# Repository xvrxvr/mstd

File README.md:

# UKNC-BK MSTD+

**UKNC-BK MSTD+** is a universal external mass storage device designed to work simultaneously with two Soviet-era 16-bit computers from the 1980s: the *Elektronika BK0010/0011* and the *Elektronika MS0511 (UKNC)*.

<https://en.wikipedia.org/wiki/Electronika_BK>

<https://en.wikipedia.org/wiki/UKNC>

Both machines are based on the K1801 series CPUs, which are compatible with the DEC PDP-11 instruction set and use a simplified version of the DEC UNIBUS-like MPI system bus.\
[Wiki MPI BUS (In Russian)](https://ru.wikipedia.org/wiki/%D0%9C%D0%B0%D0%B3%D0%B8%D1%81%D1%82%D1%80%D0%B0%D0%BB%D1%8C%D0%BD%D1%8B%D0%B9_%D0%BF%D0%B0%D1%80%D0%B0%D0%BB%D0%BB%D0%B5%D0%BB%D1%8C%D0%BD%D1%8B%D0%B9_%D0%B8%D0%BD%D1%82%D0%B5%D1%80%D1%84%D0%B5%D0%B9%D1%81)

While the physical connectors differ between the two systems (UKNC using an extended version), they are logically compatible.

To accommodate both, the board features two separate bus connectors—one for each computer.

**Key Features**

*	**Hardware**: Built on an ICE40UP5K FPGA and an ESP32 microcontroller.
*	**Display**: Includes a small OLED screen for disk image selection and device configuration.
*	**Storage**: Does **not** use SD cards. Disk images are uploaded via **Wi-Fi** and stored in the device’s internal Flash memory.
*	**Power**: USB-C connector is used **only for additional power supply**.
*	**Compatibility**: Works with both BK0010/BK0011 and UKNC (MS0511) computers.

**Current Status (July 2027)**

*	Custom PCB designed in KiCad
*	Hardware assembly and testing in progress\

# **Additional Resources**

##	📺 **Elektronika MS0511 (UKNC) Review**

*The Clueless Engineer*

[Watch on YouTube](https://www.youtube.com/watch?v=qSb77XoAgPw&ab_channel=TheCluelessEngineer)

##	📚 **DEC PDP-11 Instruction Set Reference**

Official DEC documentation archive

[View PDF](https://www.bitsavers.org/pdf/dec/pdp11/handbooks/PDP11_Handbook_1981.pdf)

##	🖥️ **UKNC Emulator**

Cross-platform emulator for Elektronika MS0511

[GitHub Repository](https://github.com/sergev/ukncbtl)

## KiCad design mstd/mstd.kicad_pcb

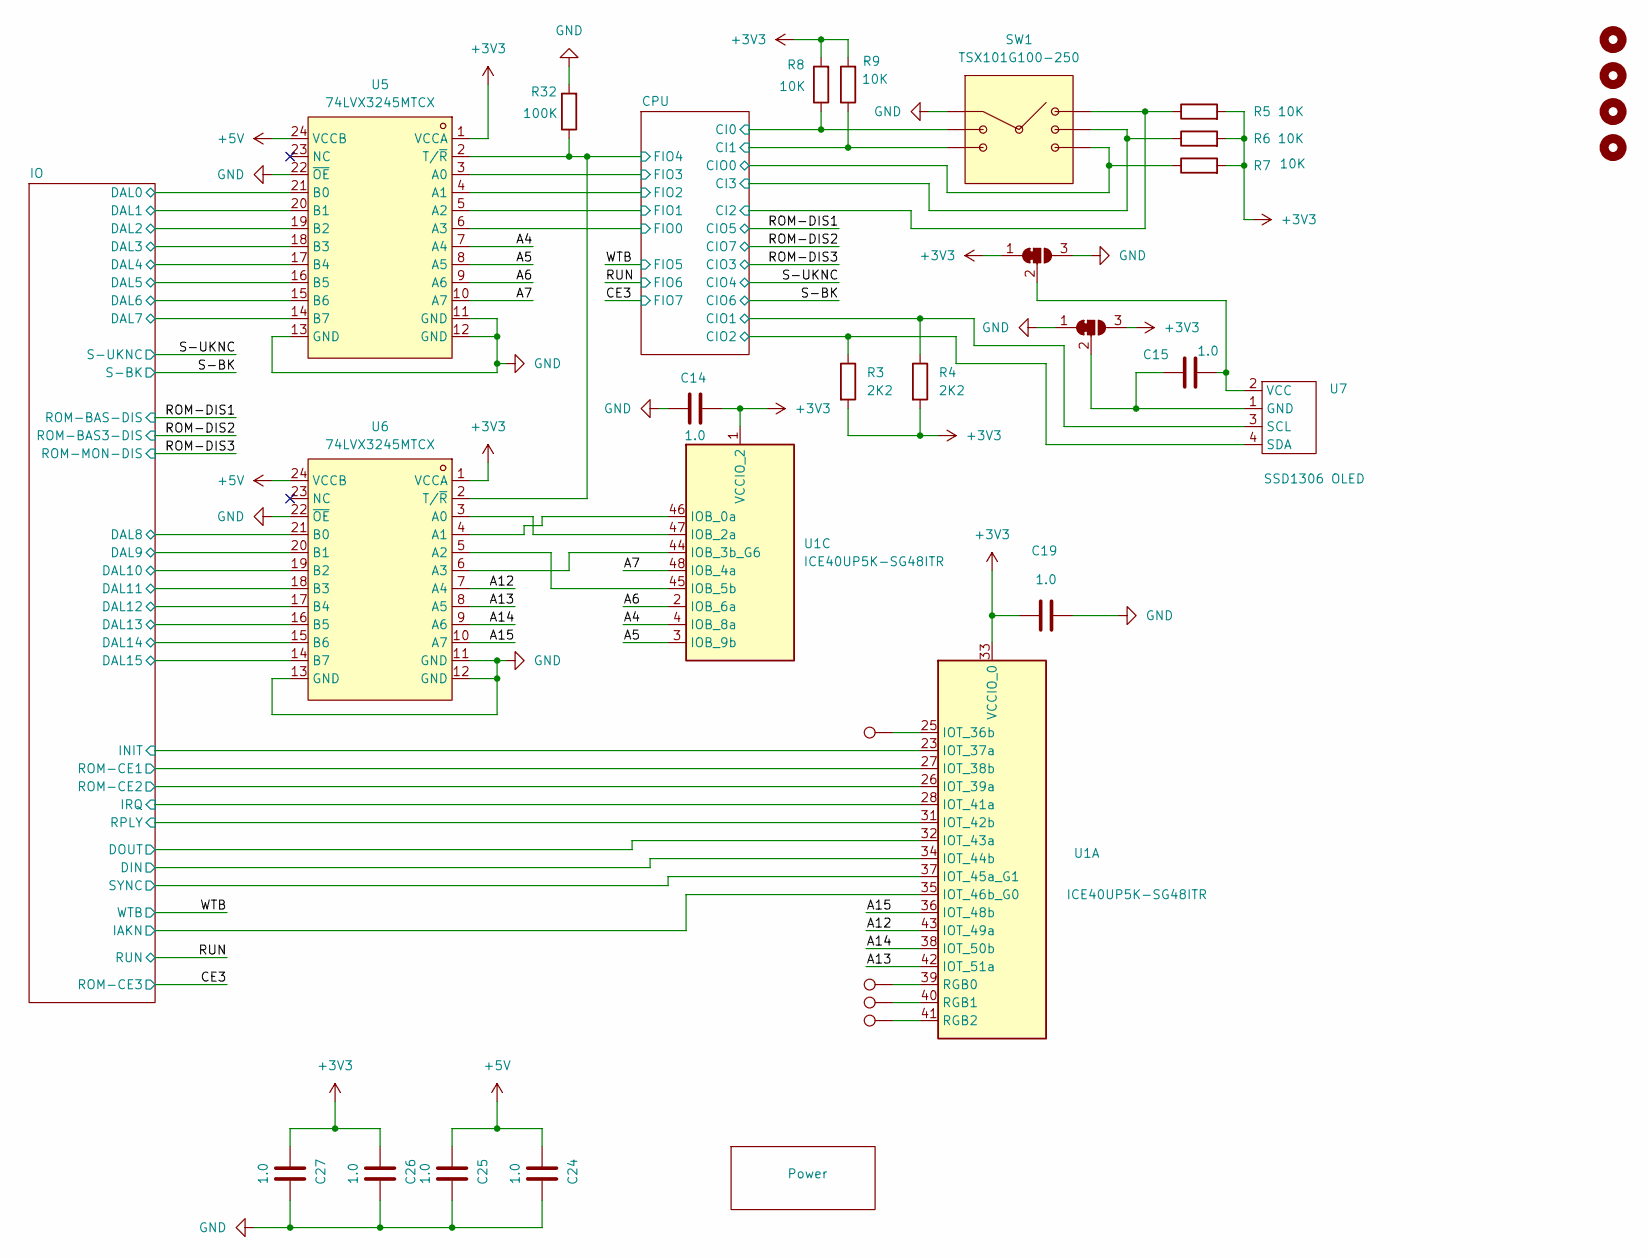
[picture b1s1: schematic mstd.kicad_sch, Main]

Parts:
C14, C15, C19, C24, C25, C26, C27: 1.0; C_0603_1608Metric_Pad1.08x0.95mm_HandSolder
H1, H2, H3, H4: MountingHole; MountingHole_3.2mm_M3_ISO14580
JP1, JP2: SolderJumper_3_Bridged12; SolderJumper-3_P1.3mm_Bridged12_RoundedPad1.0x1.5mm
R3, R4: 2K2; R_0603_1608Metric_Pad0.98x0.95mm_HandSolder
R5, R6, R7, R8, R9: 10K; R_0603_1608Metric_Pad0.98x0.95mm_HandSolder
R32: 100K; R_0603_1608Metric_Pad0.98x0.95mm_HandSolder
SW1: TSX101G100-250; SW-TH_TSX101G100-250; LCSC Part C722957
TP1, TP2, TP3, TP4: TestPoint; TestPoint_THTPad_D1.0mm_Drill0.5mm
U1: ICE40UP5K-SG48ITR; QFN-48-1EP_7x7mm_P0.5mm_EP5.6x5.6mm
U5, U6: 74LVX3245MTCX; SOP-24_7.5x15.4mm_P1.27mm; LCSC Part C6135
U7: SSD1306 OLED; SDD1306

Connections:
+3V3: C14.2, C19.1, C26.1, C27.1, JP1.1 (A), JP2.3 (B), R3.2, R4.2, R5.2, R6.2, R7.2, R8.2, R9.2, U1.1 (VCCIO_2), U1.33 (VCCIO_0), U5.1 (VCCA), U6.1 (VCCA); also elsewhere on the board
+5V: C24.1, C25.1, U5.24 (VCCB), U6.24 (VCCB); also elsewhere on the board
/A4: U1.4 (IOB_8a), U5.7 (A4)
/A5: U1.3 (IOB_9b), U5.8 (A5)
/A6: U1.2 (IOB_6a), U5.9 (A6)
/A7: U1.48 (IOB_4a), U5.10 (A7)
/A12: U1.43 (IOT_49a), U6.7 (A4)
/A13: U1.42 (IOT_51a), U6.8 (A5)
/A14: U1.38 (IOT_50b), U6.9 (A6)
/A15: U1.36 (IOT_48b), U6.10 (A7)
/CPU/CI0: R8.1, SW1.2; also elsewhere on the board
/CPU/CI1: R9.1, SW1.3; also elsewhere on the board
/CPU/CI2: R5.1, SW1.4; also elsewhere on the board
/CPU/CI3: R6.1, SW1.5; also elsewhere on the board
/CPU/CIO0: R7.1, SW1.6; also elsewhere on the board
/CPU/CIO1: R4.1, U7.3 (SCL); also elsewhere on the board
/CPU/CIO2: R3.1, U7.4 (SDA); also elsewhere on the board
/CPU/FIO0: U5.6 (A3); also elsewhere on the board
/CPU/FIO1: U5.5 (A2); also elsewhere on the board
/CPU/FIO2: U5.4 (A1); also elsewhere on the board
/CPU/FIO3: U5.3 (A0); also elsewhere on the board
/CPU/FIO4: R32.1, U5.2 (T/~R), U6.2 (T/~R); also elsewhere on the board
/IO/DAL0: U5.21 (B0); also elsewhere on the board
/IO/DAL1: U5.20 (B1); also elsewhere on the board
/IO/DAL2: U5.19 (B2); also elsewhere on the board
/IO/DAL3: U5.18 (B3); also elsewhere on the board
/IO/DAL4: U5.17 (B4); also elsewhere on the board
/IO/DAL5: U5.16 (B5); also elsewhere on the board
/IO/DAL6: U5.15 (B6); also elsewhere on the board
/IO/DAL7: U5.14 (B7); also elsewhere on the board
/IO/DAL8: U6.21 (B0); also elsewhere on the board
/IO/DAL9: U6.20 (B1); also elsewhere on the board
/IO/DAL10: U6.19 (B2); also elsewhere on the board
/IO/DAL11: U6.18 (B3); also elsewhere on the board
/IO/DAL12: U6.17 (B4); also elsewhere on the board
/IO/DAL13: U6.16 (B5); also elsewhere on the board
/IO/DAL14: U6.15 (B6); also elsewhere on the board
/IO/DAL15: U6.14 (B7); also elsewhere on the board
/IO/DIN: U1.34 (IOT_44b); also elsewhere on the board
/IO/DOUT: U1.32 (IOT_43a); also elsewhere on the board
/IO/IAKN: U1.35 (IOT_46b_G0); also elsewhere on the board
/IO/INIT: U1.23 (IOT_37a); also elsewhere on the board
/IO/IRQ: U1.28 (IOT_41a); also elsewhere on the board
/IO/ROM-CE1: U1.27 (IOT_38b); also elsewhere on the board
/IO/ROM-CE2: U1.26 (IOT_39a); also elsewhere on the board
/IO/RPLY: U1.31 (IOT_42b); also elsewhere on the board
/IO/SYNC: U1.37 (IOT_45a_G1); also elsewhere on the board
GND: C14.1, C19.2, C24.2, C25.2, C26.2, C27.2, JP1.3 (B), JP2.1 (A), R32.2, SW1.1, U5.11 (GND), U5.12 (GND), U5.13 (GND), U5.22 (~OE), U6.11 (GND), U6.12 (GND), U6.13 (GND), U6.22 (~OE); also elsewhere on the board
unnamed: C15.2, JP1.2 (C), U7.2 (VCC)
unnamed: C15.1, JP2.2 (C), U7.1 (GND)
unnamed: TP1.1, U1.25 (IOT_36b)
unnamed: TP2.1, U1.39 (RGB0)
unnamed: TP3.1, U1.40 (RGB1)
unnamed: TP4.1, U1.41 (RGB2)
unnamed: U1.46 (IOB_0a), U6.4 (A1)
unnamed: U1.47 (IOB_2a), U6.3 (A0)
unnamed: U1.44 (IOB_3b_G6), U6.6 (A3)
unnamed: U1.45 (IOB_5b), U6.5 (A2)

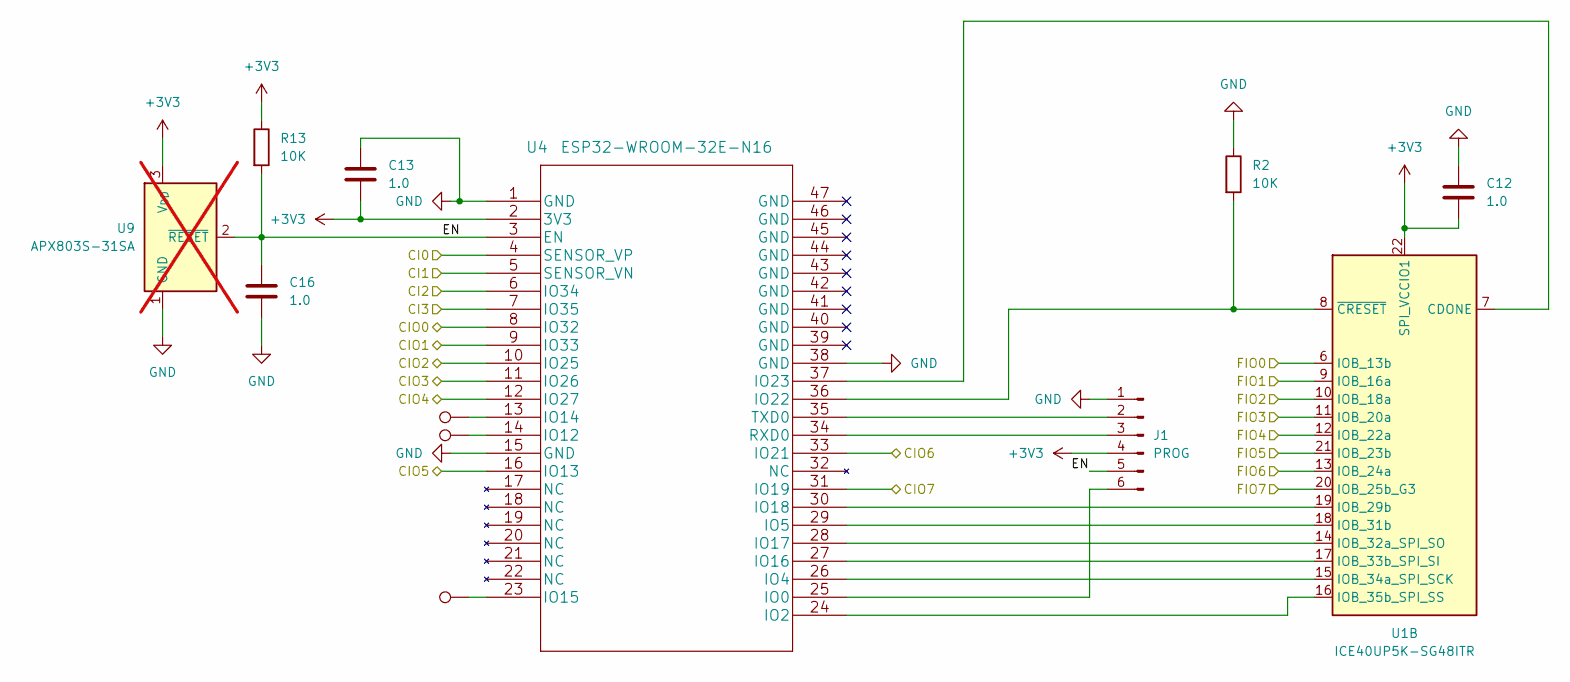
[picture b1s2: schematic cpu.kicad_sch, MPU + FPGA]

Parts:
C12, C13, C16: 1.0; C_0603_1608Metric_Pad1.08x0.95mm_HandSolder
J1: PROG; PinHeader_1x06_P2.54mm_Vertical
R2, R13: 10K; R_0603_1608Metric_Pad0.98x0.95mm_HandSolder
TP5, TP6, TP7: TestPoint; TestPoint_THTPad_D1.0mm_Drill0.5mm
U1: ICE40UP5K-SG48ITR; QFN-48-1EP_7x7mm_P0.5mm_EP5.6x5.6mm
U4: ESP32-WROOM-32E-N16; ESP32-WROOM-32E-N8
U9: APX803S-31SA; SOT-23-3; not fitted

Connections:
+3V3: C12.2, C13.2, J1.4, R13.1, U1.22 (SPI_VCCIO1), U4.2 (3V3), U9.3 (V_{DD}); also elsewhere on the board
/CE3: U1.20 (IOB_25b_G3); also elsewhere on the board
/CPU/CI0: U4.4 (SENSOR_VP); also elsewhere on the board
/CPU/CI1: U4.5 (SENSOR_VN); also elsewhere on the board
/CPU/CI2: U4.6 (IO34); also elsewhere on the board
/CPU/CI3: U4.7 (IO35); also elsewhere on the board
/CPU/CIO0: U4.8 (IO32); also elsewhere on the board
/CPU/CIO1: U4.9 (IO33); also elsewhere on the board
/CPU/CIO2: U4.10 (IO25); also elsewhere on the board
/CPU/EN: C16.1, J1.5, R13.2, U4.3 (EN), U9.2 (~RESET)
/CPU/FIO0: U1.6 (IOB_13b); also elsewhere on the board
/CPU/FIO1: U1.9 (IOB_16a); also elsewhere on the board
/CPU/FIO2: U1.10 (IOB_18a); also elsewhere on the board
/CPU/FIO3: U1.11 (IOB_20a); also elsewhere on the board
/CPU/FIO4: U1.12 (IOB_22a); also elsewhere on the board
/ROM-DIS1: U4.16 (IO13); also elsewhere on the board
/ROM-DIS2: U4.31 (IO19); also elsewhere on the board
/ROM-DIS3: U4.11 (IO26); also elsewhere on the board
/RUN: U1.13 (IOB_24a); also elsewhere on the board
/S-BK: U4.33 (IO21); also elsewhere on the board
/S-UKNC: U4.12 (IO27); also elsewhere on the board
/WTB: U1.21 (IOB_23b); also elsewhere on the board
GND: C12.1, C13.1, C16.2, J1.1, R2.1, U4.1 (GND), U4.15 (GND), U4.38 (GND), U9.1 (GND); also elsewhere on the board
unnamed: J1.2, U4.35 (TXD0)
unnamed: J1.3, U4.34 (RXD0)
unnamed: J1.6, U4.25 (IO0)
unnamed: U1.7 (CDONE), U4.37 (IO23)
unnamed: U1.19 (IOB_29b), U4.30 (IO18)
unnamed: U1.18 (IOB_31b), U4.29 (IO5)
unnamed: U1.14 (IOB_32a_SPI_SO), U4.28 (IO17)
unnamed: U1.17 (IOB_33b_SPI_SI), U4.27 (IO16)
unnamed: U1.15 (IOB_34a_SPI_SCK), U4.26 (IO4)
unnamed: U1.16 (IOB_35b_SPI_SS), U4.24 (IO2)
unnamed: R2.2, U1.8 (~CRESET), U4.36 (IO22)
unnamed: TP6.1, U4.14 (IO12)
unnamed: TP5.1, U4.13 (IO14)
unnamed: TP7.1, U4.23 (IO15)

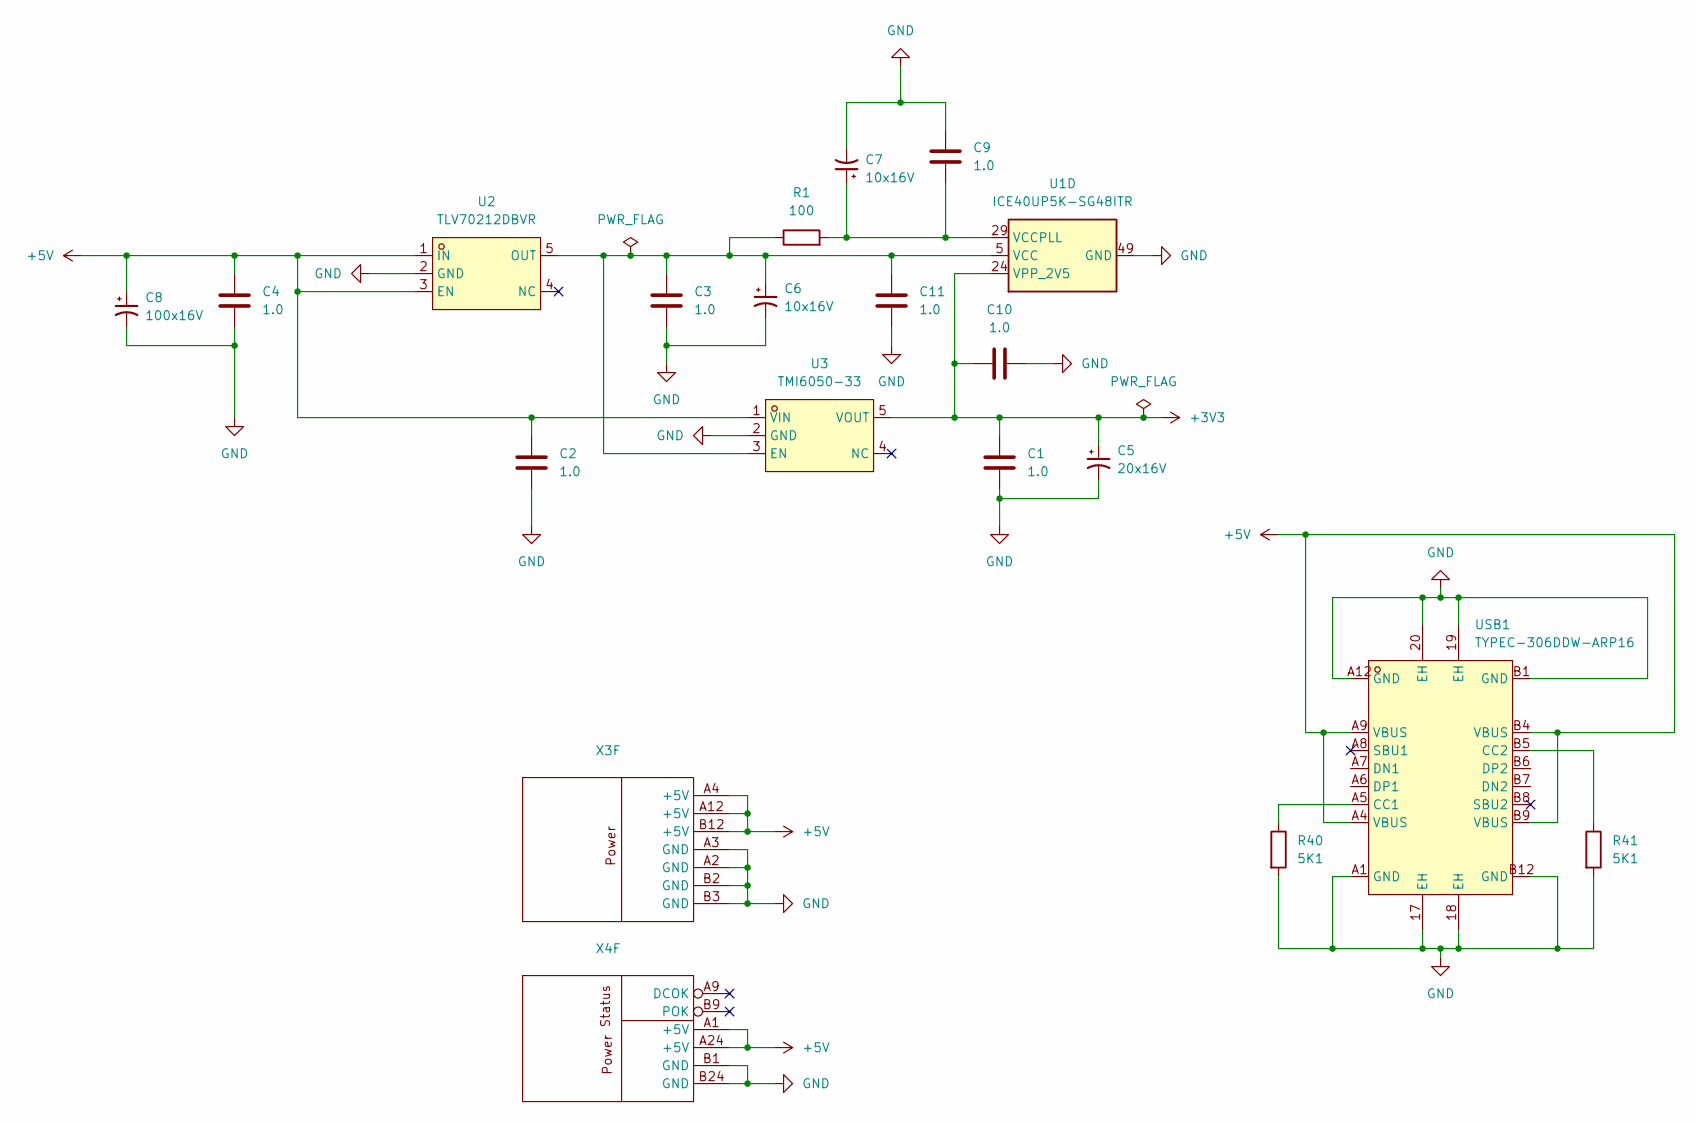
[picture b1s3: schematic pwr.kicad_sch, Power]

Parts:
C1, C2, C3, C4, C9, C10, C11: 1.0; C_0603_1608Metric_Pad1.08x0.95mm_HandSolder
C5: 20x16V; CP_Radial_D5.0mm_P2.00mm
C6, C7: 10x16V; CP_Radial_D5.0mm_P2.00mm
C8: 100x16V; CP_Radial_D6.3mm_P2.50mm
R1: 100; R_0603_1608Metric_Pad0.98x0.95mm_HandSolder
R40, R41: 5K1; R_0603_1608Metric_Pad0.98x0.95mm_HandSolder; LCSC Part C2907044
U1: ICE40UP5K-SG48ITR; QFN-48-1EP_7x7mm_P0.5mm_EP5.6x5.6mm
U2: TLV70212DBVR; SOT-23-5_L3.0-W1.7-P0.95-LS2.8-BL; LCSC Part C81462
U3: TMI6050-33; SOT-23-5_L2.9-W1.6-P0.95-LS2.8-BR; LCSC Part C911079
USB1: TYPEC-306DDW-ARP16; USB-C-TH_TYPEC-306DDW-ARP16; LCSC Part C2840393
X3: 09722642801-1
X4: snp15

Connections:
+3V3: C1.1, C5.1, C10.1, U1.24 (VPP_2V5), U3.5 (VOUT); also elsewhere on the board
+5V: C2.1, C4.1, C8.1, U2.1 (IN), U2.3 (EN), U3.1 (VIN), USB1.A4 (VBUS), USB1.A9 (VBUS), USB1.B4 (VBUS), USB1.B9 (VBUS), X3.A4 (+5V), X3.A12 (+5V), X3.B12 (+5V), X4.A1 (+5V), X4.A24 (+5V); also elsewhere on the board
GND: C1.2, C2.2, C3.2, C4.2, C5.2, C6.2, C7.2, C8.2, C9.1, C10.2, C11.2, R40.2, R41.2, U1.49 (GND), U2.2 (GND), U3.2 (GND), USB1.17 (EH), USB1.18 (EH), USB1.19 (EH), USB1.20 (EH), USB1.A1 (GND), USB1.A12 (GND), USB1.B1 (GND), USB1.B12 (GND), X3.A2 (GND), X3.A3 (GND), X3.B2 (GND), X3.B3 (GND), X4.B1 (GND), X4.B24 (GND); also elsewhere on the board
unnamed: C7.1, C9.2, R1.2, U1.29 (VCCPLL)
unnamed: C3.1, C6.1, C11.1, R1.1, U1.5 (VCC), U1.30 (VCC), U2.5 (OUT), U3.3 (EN)
unnamed: R40.1, USB1.A5 (CC1)
unnamed: R41.1, USB1.B5 (CC2)

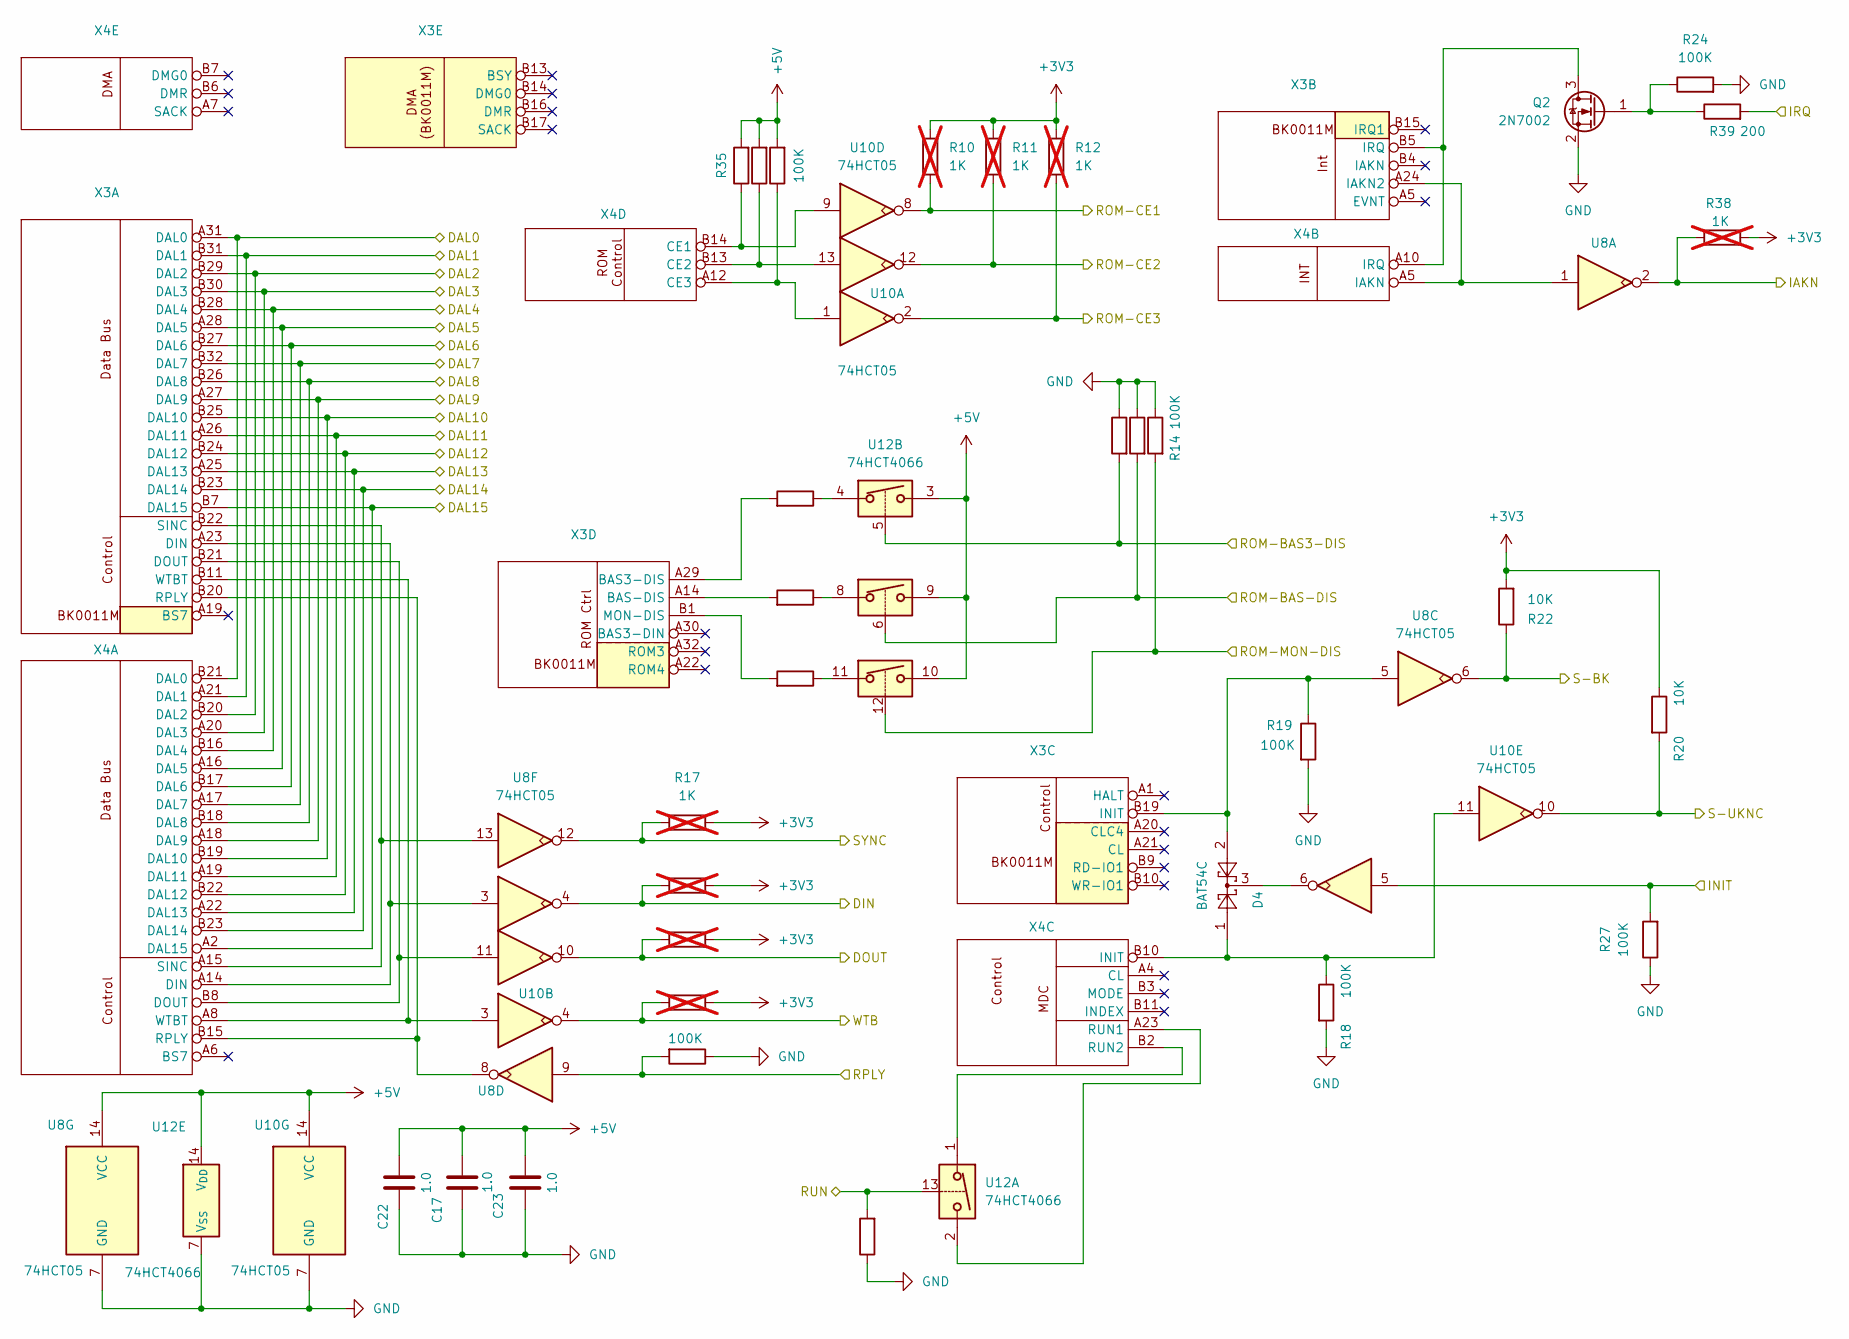
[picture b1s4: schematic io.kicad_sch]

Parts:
C17, C22, C23: 1.0; C_0603_1608Metric_Pad1.08x0.95mm_HandSolder
D4: BAT54C; SOT-23
Q2: 2N7002; SOT-23
R10, R11, R12, R17, R21, R25, R26, R38: 1K; R_0603_1608Metric_Pad0.98x0.95mm_HandSolder; not fitted
R14, R15, R16, R18, R19, R23, R24, R27, R28, R35, R36, R37: 100K; R_0603_1608Metric_Pad0.98x0.95mm_HandSolder
R20, R22: 10K; R_0603_1608Metric_Pad0.98x0.95mm_HandSolder
R29, R30, R31: R; R_0603_1608Metric_Pad0.98x0.95mm_HandSolder
R39: 200; R_0603_1608Metric_Pad0.98x0.95mm_HandSolder
U8, U10: 74HCT05; SO-14_3.9x8.65mm_P1.27mm
U12: 74HCT4066; SO-14_3.9x8.65mm_P1.27mm
X3: 09722642801-1
X4: snp15

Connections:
+3V3: R10.2, R11.2, R12.2, R17.2, R20.1, R21.2, R22.2, R25.2, R26.2, R38.1; also elsewhere on the board
+5V: C17.2, C22.2, C23.2, R35.2, R36.2, R37.2, U8.14 (VCC), U10.14 (VCC), U12.3, U12.9, U12.10, U12.14 (V_{DD}); also elsewhere on the board
/CE3: R12.1, U10.2; also elsewhere on the board
/IO/DAL0: X3.A31 (DAL0), X4.B21 (DAL0); also elsewhere on the board
/IO/DAL1: X3.B31 (DAL1), X4.A21 (DAL1); also elsewhere on the board
/IO/DAL2: X3.B29 (DAL2), X4.B20 (DAL2); also elsewhere on the board
/IO/DAL3: X3.B30 (DAL3), X4.A20 (DAL3); also elsewhere on the board
/IO/DAL4: X3.B28 (DAL4), X4.B16 (DAL4); also elsewhere on the board
/IO/DAL5: X3.A28 (DAL5), X4.A16 (DAL5); also elsewhere on the board
/IO/DAL6: X3.B27 (DAL6), X4.B17 (DAL6); also elsewhere on the board
/IO/DAL7: X3.B32 (DAL7), X4.A17 (DAL7); also elsewhere on the board
/IO/DAL8: X3.B26 (DAL8), X4.B18 (DAL8); also elsewhere on the board
/IO/DAL9: X3.A27 (DAL9), X4.A18 (DAL9); also elsewhere on the board
/IO/DAL10: X3.B25 (DAL10), X4.B19 (DAL10); also elsewhere on the board
/IO/DAL11: X3.A26 (DAL11), X4.A19 (DAL11); also elsewhere on the board
/IO/DAL12: X3.B24 (DAL12), X4.B22 (DAL12); also elsewhere on the board
/IO/DAL13: X3.A25 (DAL13), X4.A22 (DAL13); also elsewhere on the board
/IO/DAL14: X3.B23 (DAL14), X4.B23 (DAL14); also elsewhere on the board
/IO/DAL15: X3.B7 (DAL15), X4.A2 (DAL15); also elsewhere on the board
/IO/DIN: R21.1, U8.4; also elsewhere on the board
/IO/DOUT: R25.1, U8.10; also elsewhere on the board
/IO/IAKN: R38.2, U8.2; also elsewhere on the board
/IO/INIT: R27.2, U10.5; also elsewhere on the board
/IO/IRQ: R39.2; also elsewhere on the board
/IO/ROM-CE1: R10.1, U10.8; also elsewhere on the board
/IO/ROM-CE2: R11.1, U10.12; also elsewhere on the board
/IO/RPLY: R23.2, U8.9; also elsewhere on the board
/IO/SYNC: R17.1, U8.12; also elsewhere on the board
/ROM-DIS1: R15.2, U12.6; also elsewhere on the board
/ROM-DIS2: R16.2, U12.5; also elsewhere on the board
/ROM-DIS3: R14.2, U12.12; also elsewhere on the board
/RUN: R28.2, U12.13; also elsewhere on the board
/S-BK: R22.1, U8.6; also elsewhere on the board
/S-UKNC: R20.2, U10.10; also elsewhere on the board
/WTB: R26.1, U10.4; also elsewhere on the board
GND: C17.1, C22.1, C23.1, Q2.2 (S), R14.1, R15.1, R16.1, R18.2, R19.2, R23.1, R24.2, R27.1, R28.1, U8.7 (GND), U10.7 (GND), U12.7 (V_{SS}); also elsewhere on the board
unnamed: D4.3, U10.6
unnamed: Q2.3 (D), X3.B5 (IRQ), X4.A10 (IRQ)
unnamed: Q2.1 (G), R24.1, R39.1
unnamed: R29.1, U12.4
unnamed: R30.1, U12.8
unnamed: R31.1, U12.11
unnamed: U8.3, X3.A23 (DIN), X4.A14 (DIN)
unnamed: U8.11, X3.B21 (DOUT), X4.B8 (DOUT)
unnamed: U8.8, X3.B20 (RPLY), X4.B15 (RPLY)
unnamed: U8.13, X3.B22 (SINC), X4.A15 (SINC)
unnamed: U10.3, X3.B11 (WTBT), X4.A8 (WTBT)
unnamed: U8.1, X3.A24 (IAKN2), X4.A5 (IAKN)
unnamed: D4.2, R19.1, U8.5, X3.B19 (INIT)
unnamed: R29.2, X3.A29 (BAS3-DIS)
unnamed: R30.2, X3.A14 (BAS-DIS)
unnamed: R31.2, X3.B1 (MON-DIS)
unnamed: D4.1, R18.1, U10.11, X4.B10 (INIT)
unnamed: U12.2, X4.A23 (RUN1)
unnamed: U12.1, X4.B2 (RUN2)
unnamed: R35.1, U10.9, X4.B14 (CE1)
unnamed: R36.1, U10.13, X4.B13 (CE2)
unnamed: R37.1, U10.1, X4.A12 (CE3)

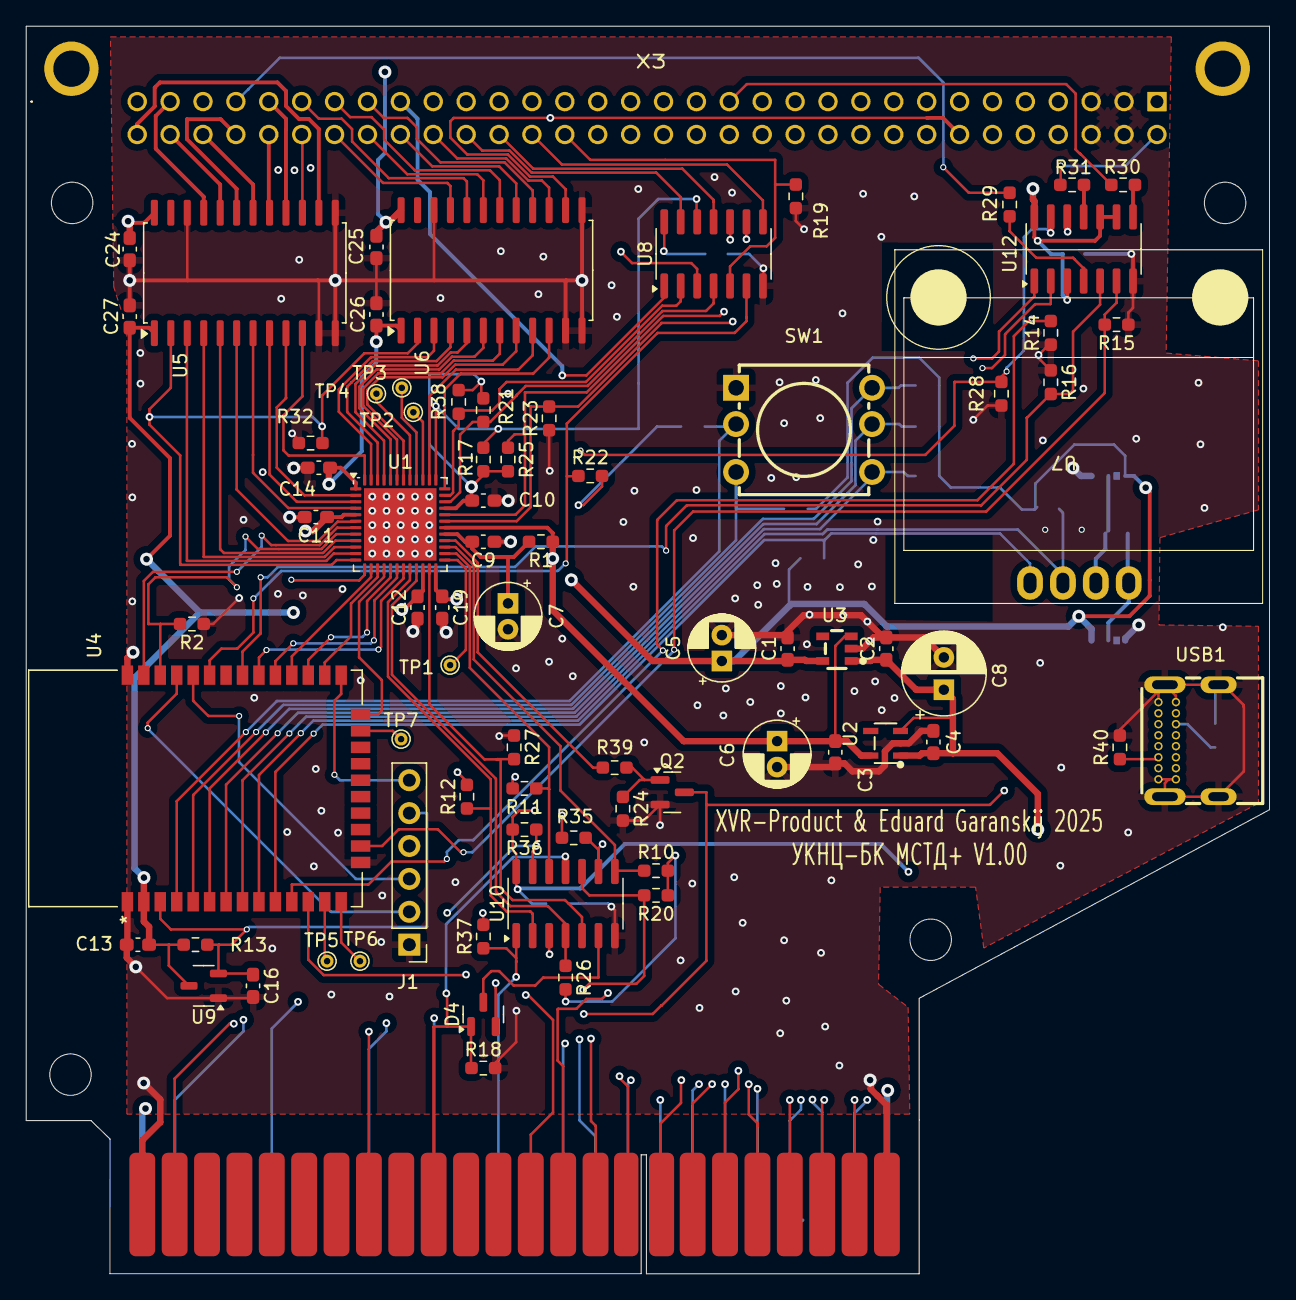
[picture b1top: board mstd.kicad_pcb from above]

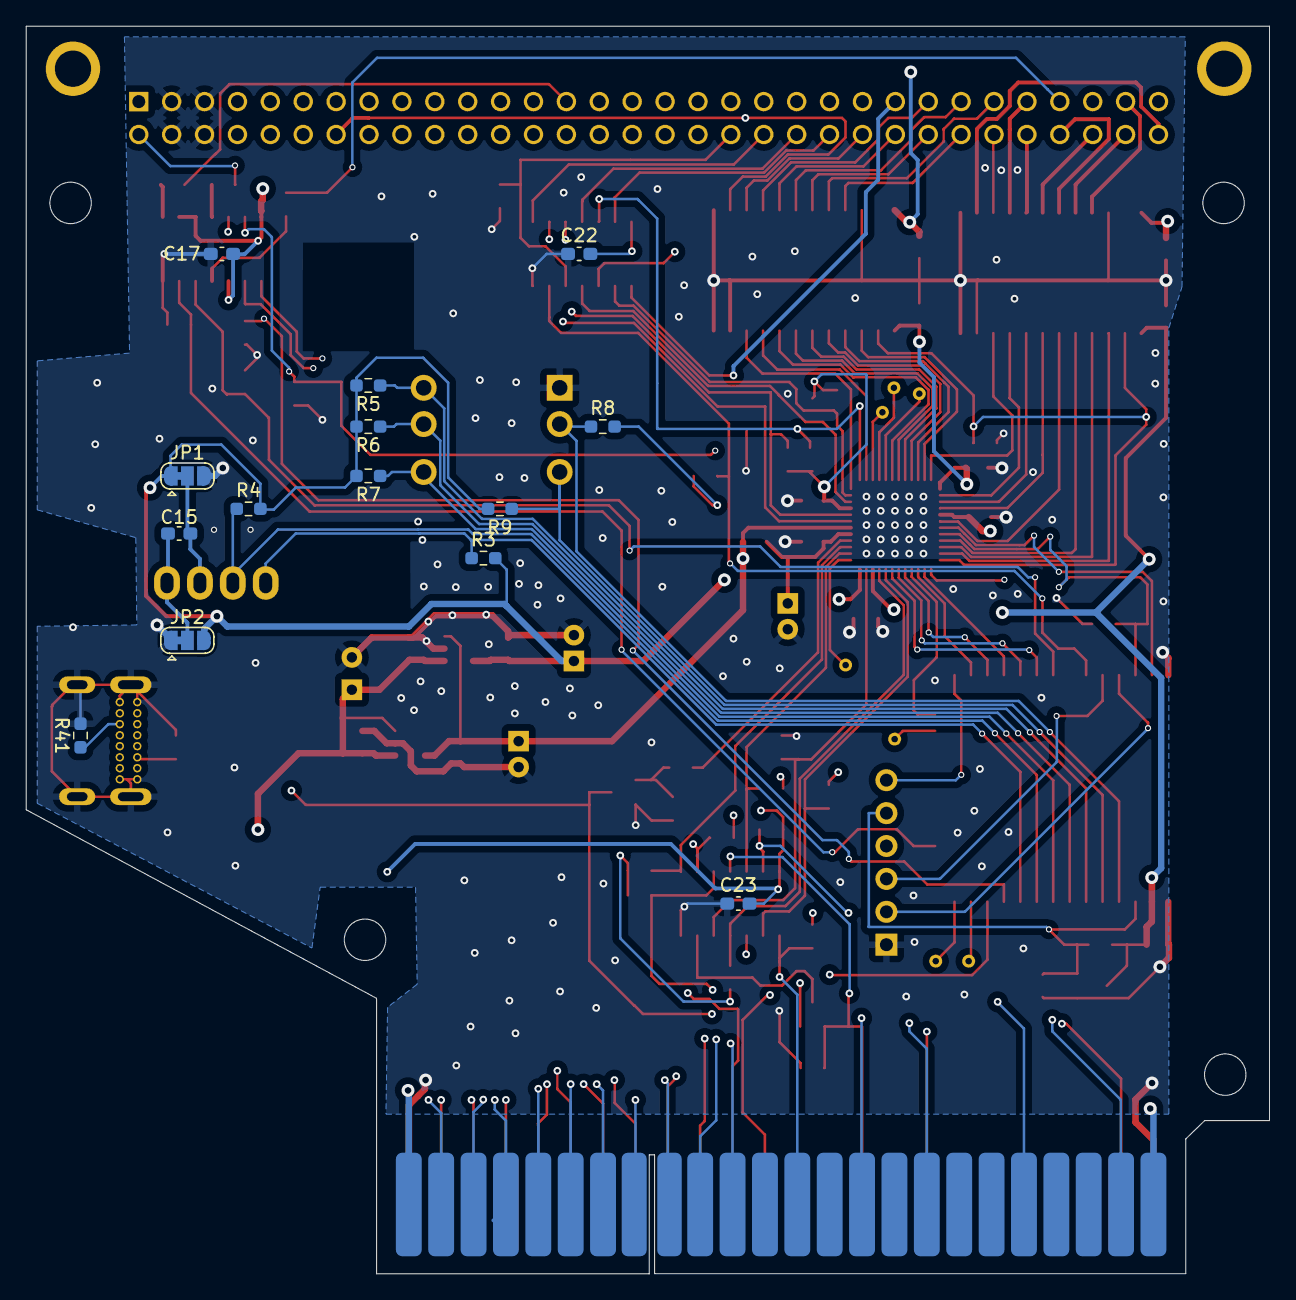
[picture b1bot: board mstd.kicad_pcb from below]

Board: 4 copper layers, 96.0 x 96.3 mm, 94 parts (14 on the bottom side), 107 nets.

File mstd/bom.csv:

"Reference","Value","Qty","DNP"
"C1,C2,C3,C4,C9,C10,C11,C12,C13,C14,C17,C19,C22,C23,C24,C25,C26,C27","1.0","18",""
"C5","20x16V","1",""
"C6,C7","10x16V","2",""
"C8","100x16V","1",""
"C20","10.0x16V","1",""
"D4","BAT54C","1",""
"J1","PROG","1",""
"J2","Barrel_Jack","1",""
"Q1","SI2301CDS-T1-GE3","1",""
"Q2","2N7002","1",""
"R1","100","1",""
"R2,R5,R6,R7,R8,R9,R13,R20,R22","10K","9",""
"R3,R4","2K2","2",""
"R10,R11,R12,R17,R21,R25,R26,R38","1K","8","DNP"
"R14,R15,R16,R18,R19,R23,R24,R27,R28,R32,R34,R35,R36,R37","100K","14",""
"R29,R30,R31","R","3",""
"R33","1K","1",""
"R39","200","1",""
"SW1","TSX101G100-250","1",""
"U1","ICE40UP5K-SG48ITR","1",""
"U2","TLV70212DBVR","1",""
"U3","TMI6050-33","1",""
"U4","ESP32-WROOM-32E-N16","1",""
"U5,U6","74LVX3245MTCX","2",""
"U7","SSD1306 OLED","1",""
"U8,U10","74HCT05","2",""
"U9","APX803S-31SA","1","DNP"
"U12","74HCT4066","1",""
"X3,X4","~","2",""

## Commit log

2025-06-07 Initial
2025-06-07 FPGA pins swapped for bring SYNC to G* pin
2025-06-07 Update schematic PDF
2025-06-07 Routing started
2025-06-07 Schematic in PDF updated
2025-06-08 Changed reset capacitor to 1.0
2025-06-08 Update Harting connector pin numeration to match SNP
2025-06-11 Routhing in finilizing stage
2025-06-11 Routing finalized
2025-06-12 Added version on PCB
2025-06-16 Added GND vias
2025-06-20 Fixes 74LVCX3245 package
2025-07-02 Finalized PCB
2025-07-23 Description added
2025-07-23 Pics update
2025-11-01 Soft updated
2025-11-05 Config Compiler update (WIP)
2026-01-02 Config processor/loader - WIP (all standalone parts done, TFTP to go)
2026-01-23 Update in Bootloader and Cfg script (now all working)
2026-02-01 Added HW FPGA Test for ESP32 (FPGA Loader). FPGA Image not ready yet
2026-02-03 Added HW test (FPGA image)
2026-02-03 Update FPGA project
2026-02-05 Added FPGA bit stream packer
2026-02-05 Added pin list file (and C sensors data)
2026-02-07 Test FW run. Fix BootLoader placement

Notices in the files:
parts and their libraries:
Copyright 2021 Accelerated Designs. All rights reserved.
